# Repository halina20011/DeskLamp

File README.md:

# Desk lap
still in dev, and untested!

## Components
Name                            | Quantity  | Cost
--------------------------------|-----------|------
ESP-01                          |     1     |   x
5mm RGB 20mA common anode       | 2 < n < 9 |   x
2k Ohm resistor                 |     3     |   x
330 Ohm resistor (r)            |     n     |   x
150 Ohm resistor (b, g)         |     n     |   x
NPN BJT 2N2222 TO-92 40V/600mA  |     3     |   x
LM317T DC linear regulator      |     1     |   x
100nF ceramic capacitor         |     1     |   x
10uF radial capacitor           |     1     |   x
1uF radial capacitor            |     1     |   x
cast acrylic sheet 4mm thick    | 69mm < x  |   x
capacitive touch sensor         |     1     |   x

## Case
If you have 3D printer you can use [deskLampHolder.FCStd](Model/deskLampHolder.FCStd) (modeling is still in the progress) </br>
if you prefer Laser cutter use [deskLampCNC.FCStd](Model/deskLampCNC.FCStd) ([cncCut.svg](Model/Export/cncCut.svg)) the model is for 4mm thick material

## Image
the image/acrilyc sheet base should be 70mm width and 10mm height

## Datasheets
[ESP8266 programming docs](https://docs.espressif.com/projects/esp8266-rtos-sdk/en/latest/get-started/index.html) </br>
[ESP-01 docs](https://docs.ai-thinker.com/_media/esp8266/docs/esp-01_product_specification_en.pdf) </br>
[ESP-01 docs](https://www.microchip.ua/wireless/esp01.pdf) </br>
[LM317T](https://www.st.com/resource/en/datasheet/lm317.pdf) </br>

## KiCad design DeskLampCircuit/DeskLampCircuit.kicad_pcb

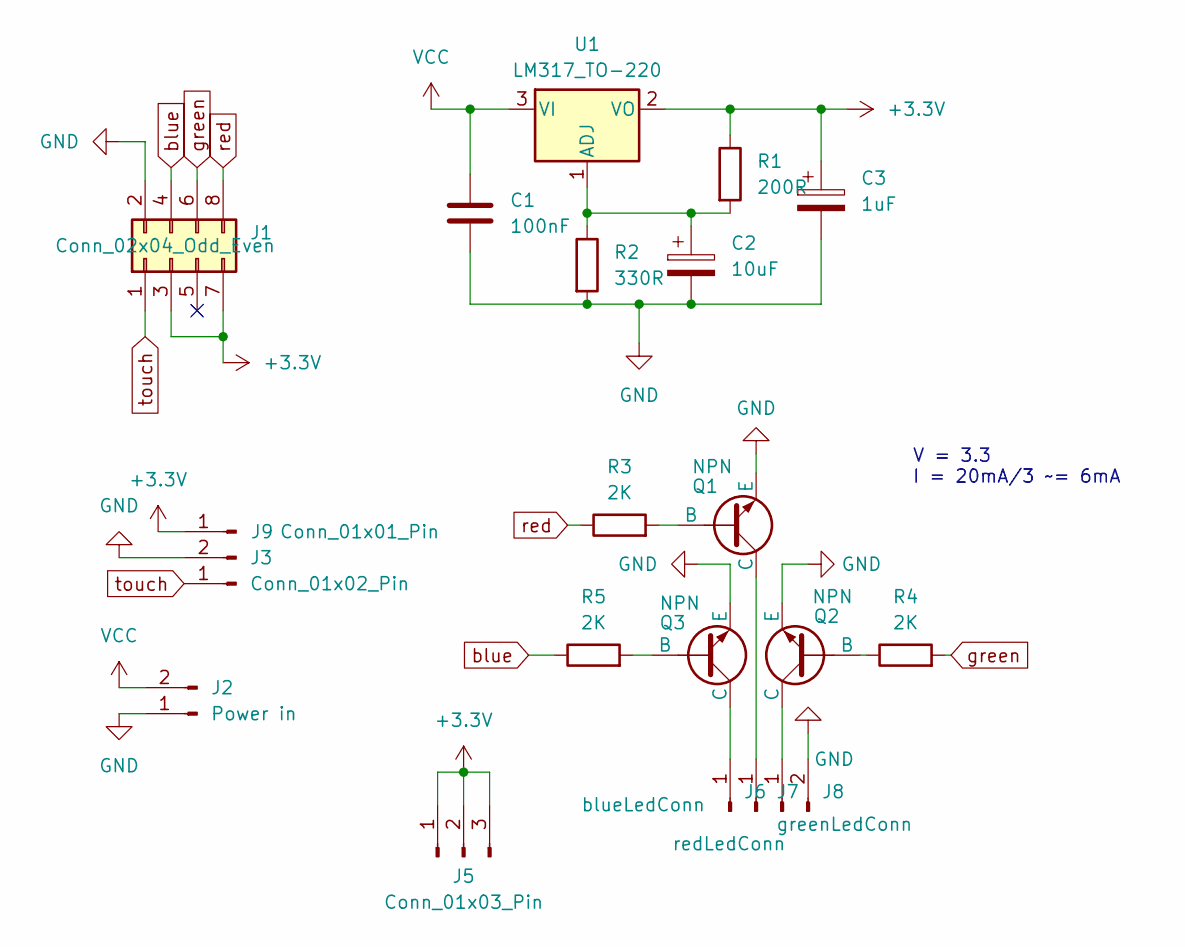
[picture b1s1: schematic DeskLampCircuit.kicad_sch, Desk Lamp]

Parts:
C1: 100nF; C_Disc_D5.0mm_W2.5mm_P5.00mm
C2: 10uF; CP_Radial_D5.0mm_P2.00mm
C3: 1uF; CP_Radial_D4.0mm_P2.00mm
J1: Conn_02x04_Odd_Even; PinHeader_2x04_P2.54mm_Vertical
J2: Power in; PinSocket_1x02_P2.54mm_Vertical
J3: Conn_01x02_Pin; PinHeader_1x02_P2.54mm_Vertical
J5: Conn_01x03_Pin; PinHeader_1x03_P2.54mm_Vertical
J6: blueLedConn; PinHeader_1x01_P2.54mm_Vertical
J7: redLedConn; PinHeader_1x01_P2.54mm_Vertical
J8: greenLedConn; PinHeader_1x02_P2.54mm_Vertical
J9: Conn_01x01_Pin; PinHeader_1x01_P2.54mm_Vertical
Q1, Q2, Q3: NPN; TO-92
R1: 200R; R_Axial_DIN0207_L6.3mm_D2.5mm_P7.62mm_Horizontal
R2: 330R; R_Axial_DIN0207_L6.3mm_D2.5mm_P7.62mm_Horizontal
R3, R4, R5: 2K; R_Axial_DIN0207_L6.3mm_D2.5mm_P7.62mm_Horizontal
U1: LM317_TO-220; TO-220-3_Vertical

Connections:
+3.3V: C3.1, J1.3, J1.7, J5.1, J5.2, J5.3, J9.1, R1.1, U1.2 (VO)
GND: C1.2, C2.2, C3.2, J1.2, J2.1, J3.2, J8.2, Q1.3 (E), Q2.3 (E), Q3.3 (E), R2.2
unnamed: J6.1, Q3.1 (C)
unnamed: J7.1, Q1.1 (C)
unnamed: J8.1, Q2.1 (C)
unnamed: Q1.2 (B), R3.2
unnamed: Q2.2 (B), R4.1
unnamed: Q3.2 (B), R5.2
unnamed: C2.1, R1.2, R2.1, U1.1 (ADJ)
VCC: C1.1, J2.2, U1.3 (VI)
blue: J1.4, R5.1
green: J1.6, R4.2
red: J1.8, R3.1
touch: J1.1, J3.1

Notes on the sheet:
V = 3.3 I = 20mA/3 ~= 6mA

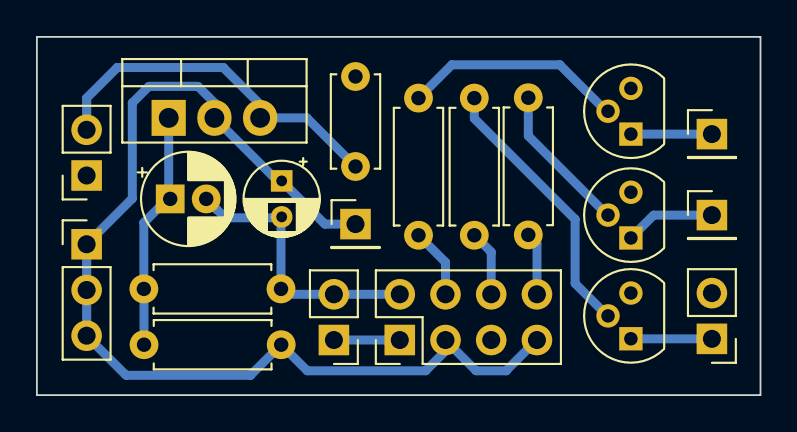
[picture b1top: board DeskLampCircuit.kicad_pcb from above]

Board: 2 copper layers, 40.2 x 19.9 mm, 20 parts (0 on the bottom side), 14 nets.

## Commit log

2024-01-11 initial layout
2024-02-01 new pcb for leds
